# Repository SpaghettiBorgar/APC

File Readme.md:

# Atari Punk Console
Simple NE555-based synthesizer toy

> [!CAUTION]
> Output stage is broken in current revision; Do not replicate.

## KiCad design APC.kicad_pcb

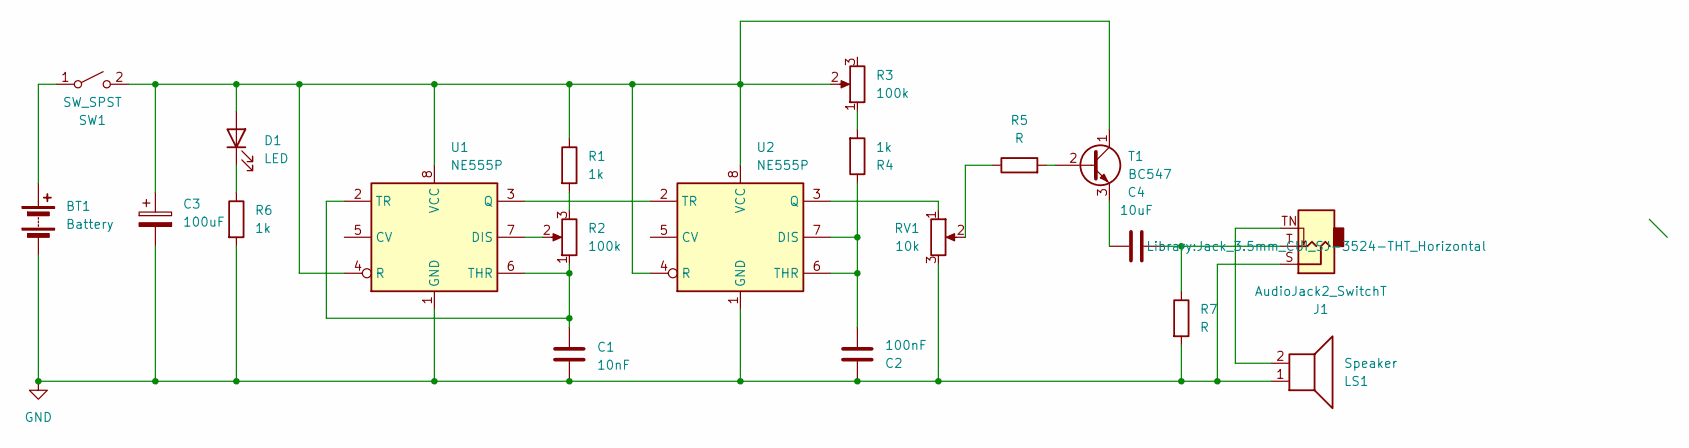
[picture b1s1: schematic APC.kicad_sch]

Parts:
BT1: Battery; PinHeader_1x02_P2.54mm_Vertical
C1: 10nF; C_Disc_D8.0mm_W2.5mm_P5.00mm
C2: 100nF; C_Disc_D8.0mm_W2.5mm_P5.00mm
C3: 100uF; CP_Radial_D6.3mm_P2.50mm
C4: 10uF; CP_Radial_D5.0mm_P2.50mm
D1: LED; LED_D5.0mm
J1: AudioJack2_SwitchT; Jack_3.5mm_CUI_SJ-3524-THT_Horizontal
LS1: Speaker; TerminalBlock_Altech_AK300-2_P5.00mm
R1, R4, R6: 1k; R_Axial_DIN0207_L6.3mm_D2.5mm_P10.16mm_Horizontal
R2, R3: 100k; Potentiometer_Alps_RK09K_Single_Vertical
R5, R7: R; R_Axial_DIN0207_L6.3mm_D2.5mm_P10.16mm_Horizontal
RV1: 10k; Rotary poti
SW1: SW_SPST; SW_E-Switch_EG1224_SPDT_Angled
T1: BC547; TO-92_Inline
U1, U2: NE555P; DIP-8_W7.62mm

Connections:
GND: BT1.2 (-), C1.2, C2.1, C3.2, J1.S, LS1.1, R6.2, R7.2, RV1.3, U1.1 (GND), U2.1 (GND)
unnamed: BT1.1 (+), SW1.1 (A)
unnamed: C4.2, J1.T, R7.1
unnamed: C3.1, D1.2 (A), R1.1, R3.2, SW1.2 (B), T1.1 (C), U1.4 (R), U1.8 (VCC), U2.4 (R), U2.8 (VCC)
unnamed: D1.1 (K), R6.1
unnamed: J1.TN, LS1.2
unnamed: R1.2, R2.3
unnamed: R3.1, R4.2
unnamed: R5.1, RV1.2
unnamed: R5.2, T1.2 (B)
unnamed: C4.1, T1.3 (E)
unnamed: R2.2, U1.7 (DIS)
unnamed: U1.3 (Q), U2.2 (TR)
unnamed 13: C1.1, R2.1, U1.2 (TR), U1.6 (THR); also elsewhere on the board
unnamed: C2.2, R4.1, U2.6 (THR), U2.7 (DIS)
unnamed: RV1.1, U2.3 (Q)

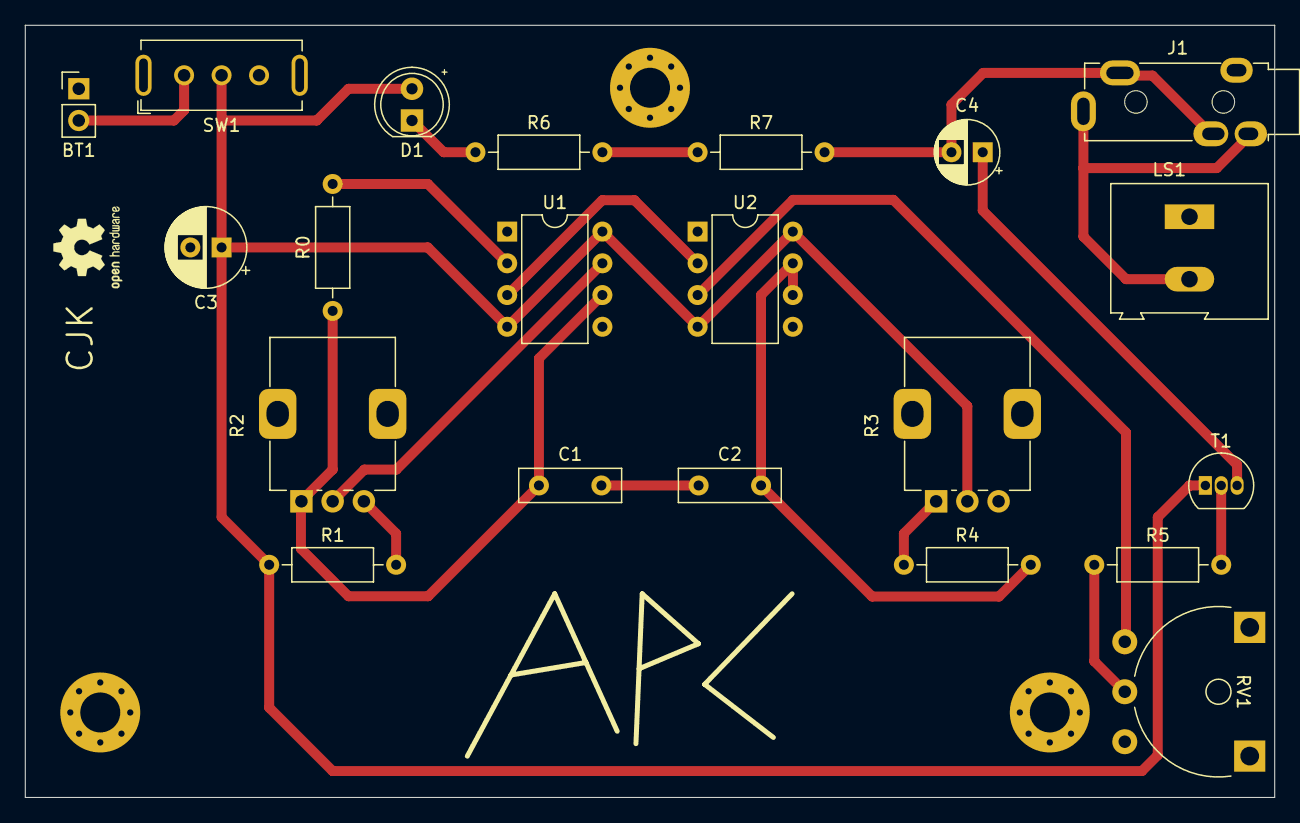
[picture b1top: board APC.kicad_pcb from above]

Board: 2 copper layers, 100.0 x 61.8 mm, 21 parts (0 on the bottom side), 16 nets.

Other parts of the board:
R0: 0; R_Axial_DIN0207_L6.3mm_D2.5mm_P10.16mm_Horizontal

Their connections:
unnamed 13: R0.1; also elsewhere on the board

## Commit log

2025-02-21 Revision 1
2025-08-19 Add Readme
